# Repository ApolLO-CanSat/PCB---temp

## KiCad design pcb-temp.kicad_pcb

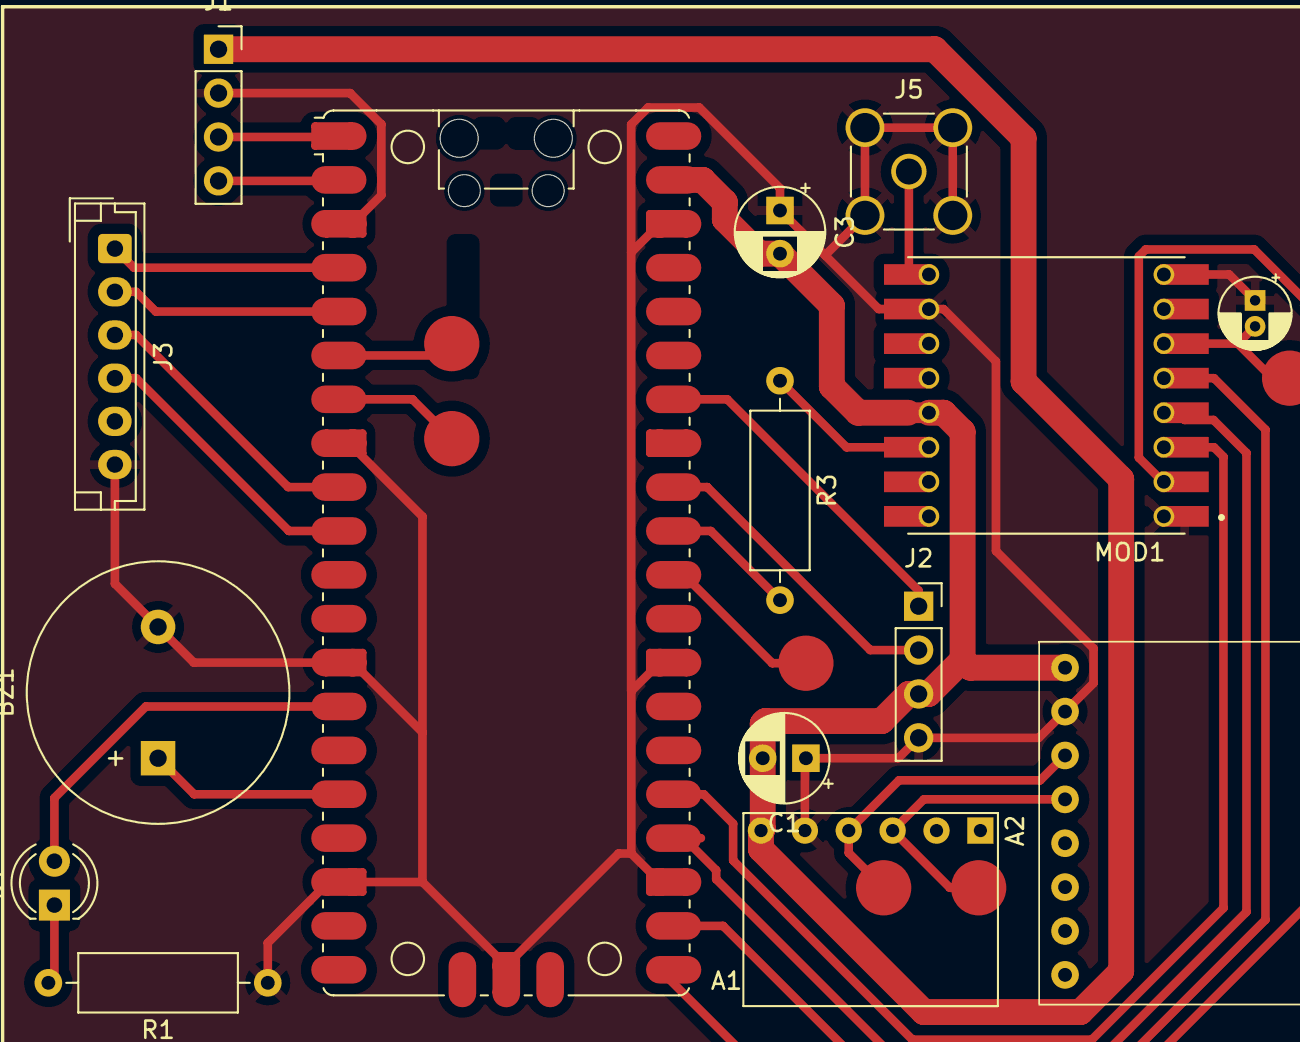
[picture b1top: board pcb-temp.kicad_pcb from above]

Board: 2 copper layers, 15 parts (0 on the bottom side), 23 nets.

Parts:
A1: RaspberryPi_Pico; RaspberryPi_Pico_Original_SMD_HandSolder
A2: BMP280_Module
BZ1: Buzzer; Buzzer_15x7.5RM7.6
C1, C3: 100u; CP_Radial_D5.0mm_P2.50mm
C4: 100n; CP_Radial_D4.0mm_P1.50mm
D1: LED; LED_D4.0mm
J1, J2: Conn_01x04_Pin; PinSocket_1x04_P2.54mm_Vertical
J3: Conn_01x06_Socket; JST_EH_B6B-EH-A_1x06_P2.50mm_Vertical
J5: Conn_Coaxial_Small; SMA_Amphenol_901-144_Vertical
MOD1: RFM98W-433S2; XCVR_RFM98W-433S2
MPU1: MPU6050
R1: 220; R_Axial_DIN0309_L9.0mm_D3.2mm_P12.70mm_Horizontal
R3: 100; R_Axial_DIN0309_L9.0mm_D3.2mm_P12.70mm_Horizontal

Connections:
+3V3: A1.39 (VSYS), A2.1 (VCC), C1.2, C3.2, J1.1, J2.3, MOD1.13 (3.3V), MOD1.13_1 (3.3V), MPU1.1 (VCC)
BUZZER: A1.16 (GPIO12), BZ1.1 (+)
DSHOT-1: A1.4 (GPIO2), J3.1
DSHOT-2: A1.5 (GPIO3), J3.2
DSHOT-3: A1.9 (GPIO6), J3.3
DSHOT-4: A1.10 (GPIO7), J3.4
GND: A1.3 (GND), A1.8 (GND), A1.13 (GND), A1.18 (GND), A1.23 (GND), A1.28 (GND), A1.38 (GND), A1.D2 (GND), A2.2 (GND), BZ1.2 (-), C1.1, C3.1, C4.1, J1.2, J2.4, J3.6, J5.2 (Ext), MOD1.1 (GND), MOD1.1_1 (GND), MOD1.8 (GND), MOD1.8_1 (GND), MOD1.10 (GND), MOD1.10_1 (GND), MPU1.2 (GND), R1.1
I2C SCL: A1.6 (GPIO4), A2.3 (SCL), MPU1.3 (SCL)
I2C SDA: A1.7 (GPIO5), A2.4 (SDA), MPU1.4 (SDA)
LoRa reset: A1.30 (RUN), C4.2, MOD1.6 (RESET), MOD1.6_1 (RESET)
unnamed: D1.1 (K), R1.2
unnamed: J5.1 (In), MOD1.9 (ANT), MOD1.9_1 (ANT)
unnamed: MOD1.14 (DIO0), MOD1.14_1 (DIO0), R3.1
PYRO 1: A1.32 (GPIO27_ADC1), J2.2
PYRO 2: A1.34 (GPIO28_ADC2), J2.1
RADIO RX INT: A1.31 (GPIO26_ADC0), R3.2
RED_LED: A1.14 (GPIO10), D1.2 (A)
SPI MISO: A1.21 (GPIO16), MOD1.2 (MISO), MOD1.2_1 (MISO)
SPI MOSI: A1.25 (GPIO19), MOD1.3 (MOSI), MOD1.3_1 (MOSI)
SPI NSS: A1.22 (GPIO17), MOD1.5 (NSS), MOD1.5_1 (NSS)
SPI SCK: A1.24 (GPIO18), MOD1.4 (SCK), MOD1.4_1 (SCK)
UART RX: A1.2 (GPIO1), J1.4
UART TX: A1.1 (GPIO0), J1.3

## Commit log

2026-01-20 added MEMS, GNSS, BMP280 and buzzer
2026-01-21 added DSHOT, led, pyro channels
2026-01-23 added LoRa and corrected connections
2026-01-26 changed pico's pinout and added ports to connect with other board
2026-01-27 finished pcb layout
2026-01-27 finished pcb layout'
2026-01-28 thickened 3V3 path
